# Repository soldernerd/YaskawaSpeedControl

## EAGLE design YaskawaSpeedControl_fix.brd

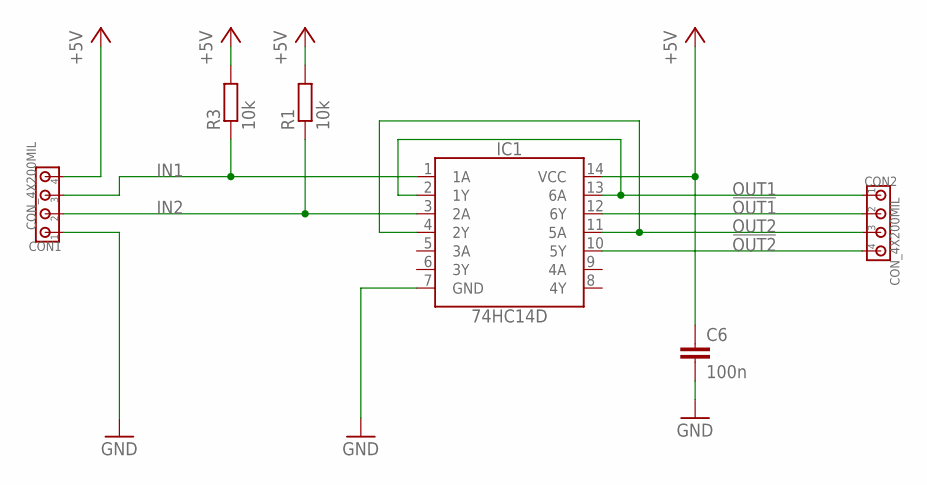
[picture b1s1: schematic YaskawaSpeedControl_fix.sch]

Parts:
C6: 100n; C0805
CON1, CON2: CON_4X200MIL; 200MIL_4X
IC1: 74HC14D; SO14
R1, R3: 10k; R0805

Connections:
!OUT1!: CON2.2, IC1.12 (6Y)
!OUT2!: CON2.4, IC1.10 (5Y)
+5V: C6.1, CON1.4, IC1.14 (VCC), R1.2, R3.2
GND: C6.2, CON1.1, IC1.7 (GND)
IN1: CON1.3, IC1.1 (1A), R3.1
IN2: CON1.2, IC1.3 (2A), R1.1
OUT1: CON2.1, IC1.2 (1Y), IC1.13 (6A)
OUT2: CON2.3, IC1.4 (2Y), IC1.11 (5A)

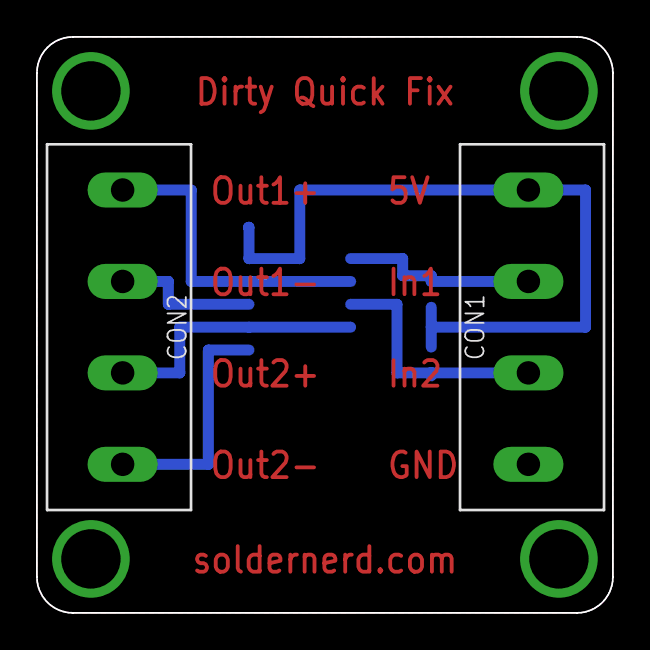
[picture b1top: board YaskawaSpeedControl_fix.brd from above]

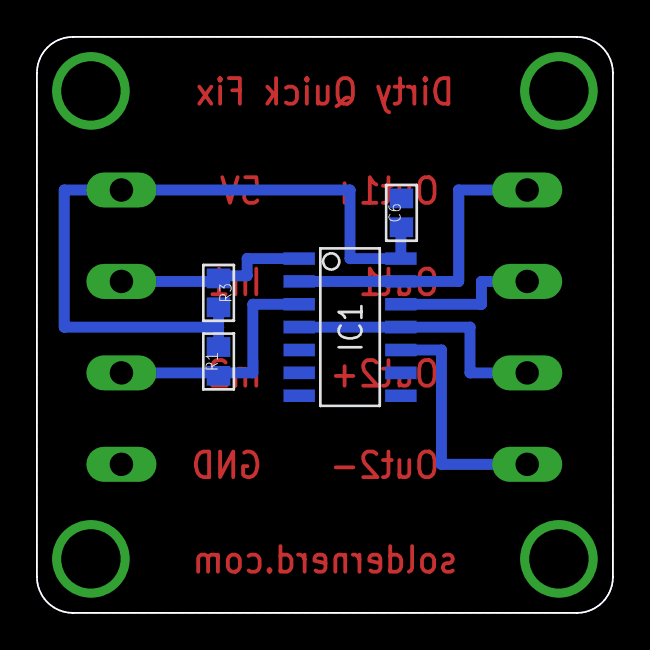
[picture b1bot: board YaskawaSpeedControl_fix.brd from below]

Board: 2 copper layers, 32.0 x 32.0 mm, 6 parts (4 on the bottom side), 8 nets.

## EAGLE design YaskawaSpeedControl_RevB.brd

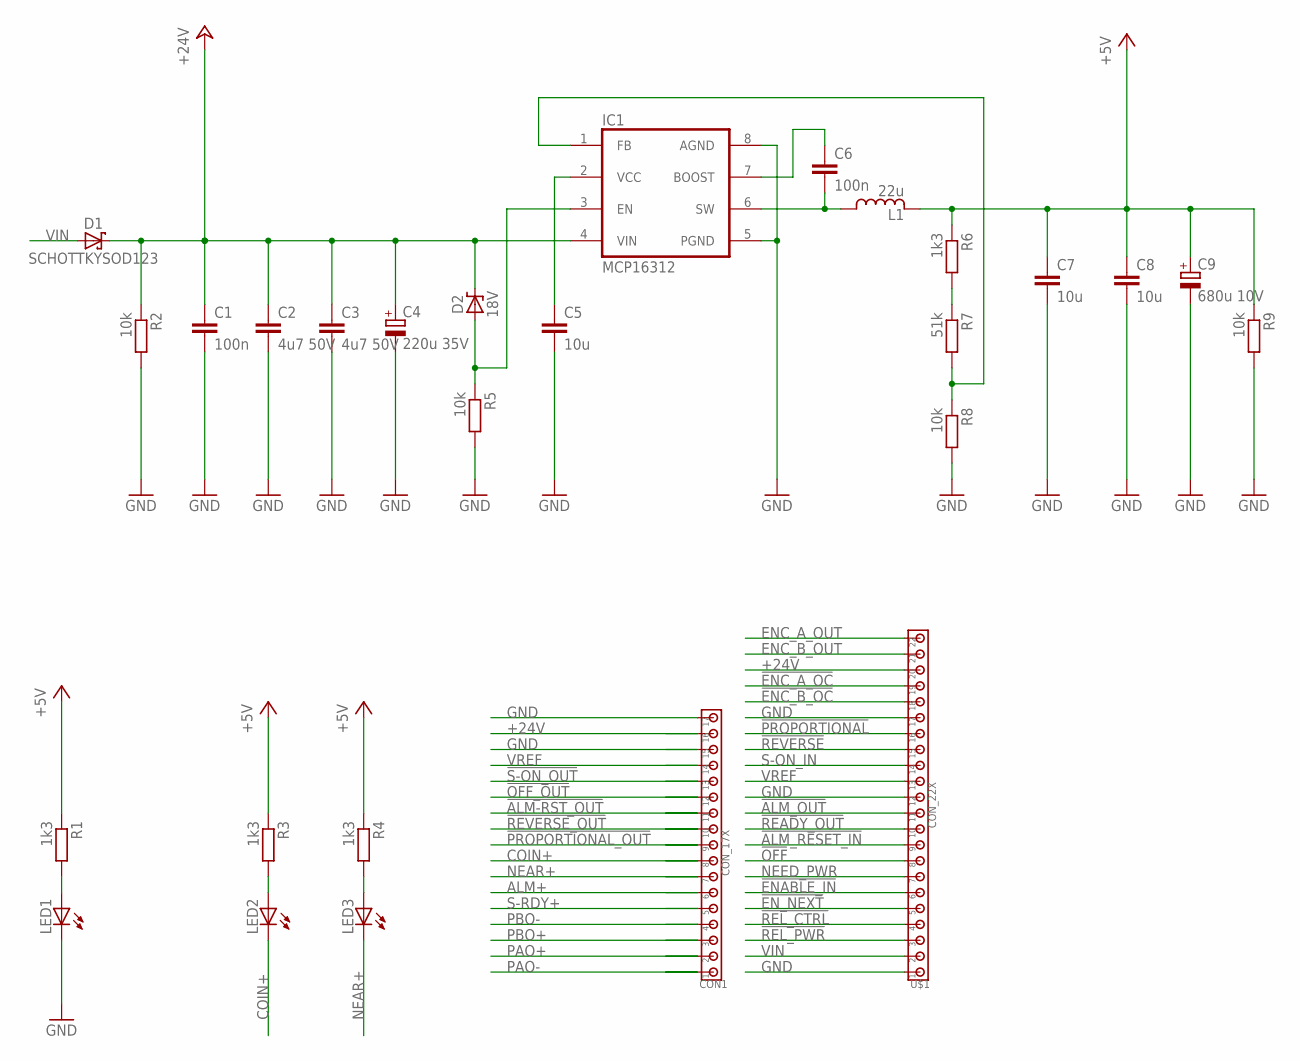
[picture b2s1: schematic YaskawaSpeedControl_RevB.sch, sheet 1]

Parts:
C1, C6: 100n; C0805
C2, C3: 4u7 50V; C1206
C4: 220u 35V; 8MM
C5, C7, C8: 10u; C0805
C9: 680u 10V; 8MM
CON1: CON_17X; 3.5MM_17X
D1: SCHOTTKYSOD123; SOD123
D2: 18V; SOD323
IC1: MCP16312; MSOP8
L1: 22u; LPS4018
LED1, LED2, LED3: LED0805_NB; LED0805_NOBOARDER
R1, R3, R4, R6: 1k3; R0805
R2, R5, R8, R9: 10k; R0805
R7: 51k; R0805
U$1: CON_22X; 3.5MM_22X

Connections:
!ALM-RST_OUT!: CON1.11; also elsewhere on the board
!ALM_OUT!: U$1.11; also elsewhere on the board
!ALM_RESET_IN!: U$1.9; also elsewhere on the board
!ENABLE_IN!: U$1.6; also elsewhere on the board
!ENC_A_OC!: U$1.19; also elsewhere on the board
!ENC_B_OC!: U$1.18; also elsewhere on the board
!EN_NEXT!: U$1.5; also elsewhere on the board
!OFF!: U$1.8; also elsewhere on the board
!OFF_OUT!: CON1.12; also elsewhere on the board
!PROPORTIONAL!: U$1.16; also elsewhere on the board
!PROPORTIONAL_OUT!: CON1.9; also elsewhere on the board
!READY_OUT!: U$1.10; also elsewhere on the board
!REL_CTRL!: U$1.4; also elsewhere on the board
!REL_PWR!: U$1.3; also elsewhere on the board
!REVERSE!: U$1.15; also elsewhere on the board
!REVERSE_OUT!: CON1.10; also elsewhere on the board
!S-ON_OUT!: CON1.13; also elsewhere on the board
+5V: C7.1, C8.1, C9.+, L1.2, R1.1, R3.1, R4.1, R6.1, R9.1; also elsewhere on the board
+24V: C1.1, C2.1, C3.1, C4.+, CON1.16, D1.C, D2.C, IC1.4 (VIN), R2.1, U$1.20; also elsewhere on the board
ALM+: CON1.6; also elsewhere on the board
BOOST: C6.1, IC1.7 (BOOST)
COIN+: CON1.8, LED2.C
ENC_A_OUT: U$1.22; also elsewhere on the board
ENC_B_OUT: U$1.21; also elsewhere on the board
GND: C1.2, C2.2, C3.2, C4.-, C5.2, C7.2, C8.2, C9.-, CON1.15, CON1.17, IC1.5 (PGND), IC1.8 (AGND), LED1.C, R2.2, R5.2, R8.2, R9.2, U$1.1, U$1.12, U$1.17; also elsewhere on the board
unnamed: IC1.1 (FB), R7.2, R8.1
unnamed: LED2.A, R3.2
unnamed: LED3.A, R4.2
unnamed: LED1.A, R1.2
unnamed: D2.A, IC1.3 (EN), R5.1
unnamed: R6.2, R7.1
unnamed: C5.1, IC1.2 (VCC)
NEAR+: CON1.7, LED3.C
NEED_PWR: U$1.7; also elsewhere on the board
PAO+: CON1.2; also elsewhere on the board
PAO-: CON1.1; also elsewhere on the board
PBO+: CON1.3; also elsewhere on the board
PBO-: CON1.4; also elsewhere on the board
S-ON_IN: U$1.14; also elsewhere on the board
S-RDY+: CON1.5; also elsewhere on the board
SWITCH: C6.2, IC1.6 (SW), L1.1
VIN: D1.A, U$1.2
VREF: CON1.14, U$1.13

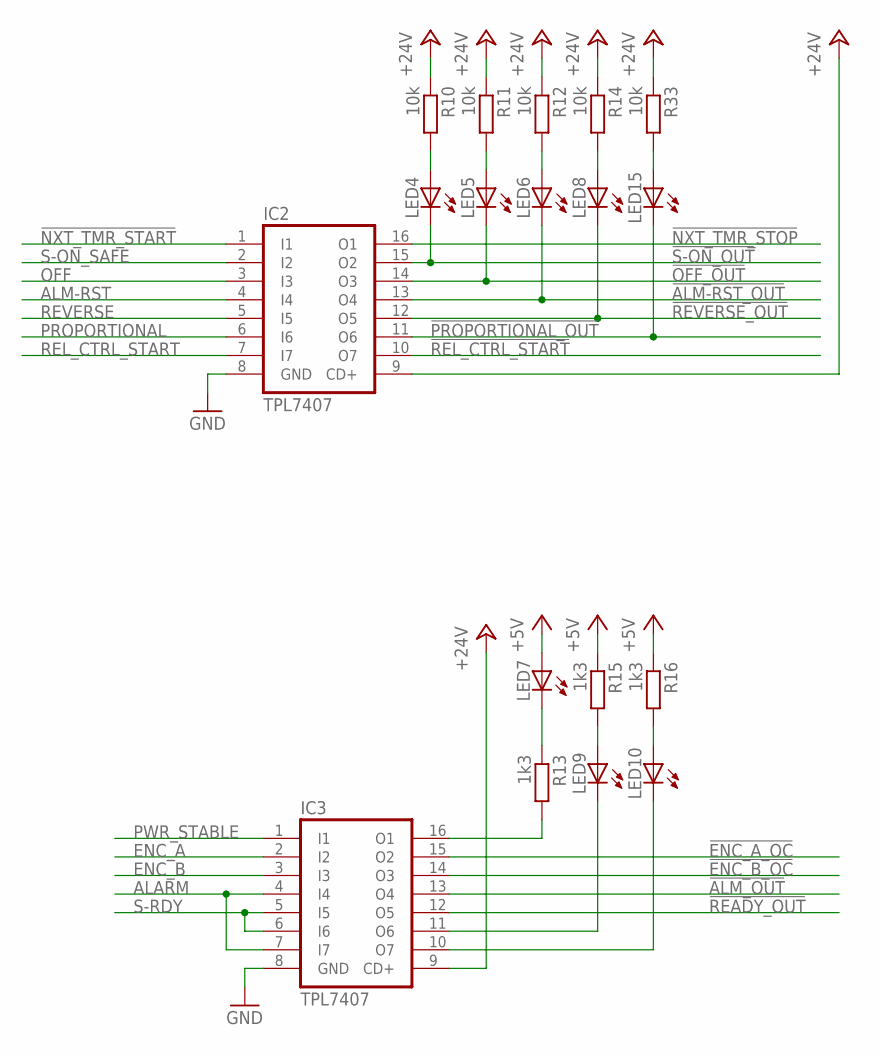
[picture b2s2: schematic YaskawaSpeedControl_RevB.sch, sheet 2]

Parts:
IC2, IC3: TPL7407; SO16
LED4, LED5, LED6, LED7, LED8, LED9, LED10, LED15: LED0805_NB; LED0805_NOBOARDER
R10, R11, R12, R14, R33: 10k; R0805
R13, R15, R16: 1k3; R0805

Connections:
!ALM-RST_OUT!: IC2.13 (O4), LED6.C; also elsewhere on the board
!ALM_OUT!: IC3.13 (O4); also elsewhere on the board
!ALM_OUT_LED!: IC3.10 (O7), LED10.C
!ENC_A_OC!: IC3.15 (O2); also elsewhere on the board
!ENC_B_OC!: IC3.14 (O3); also elsewhere on the board
!NXT_TMR_START!: IC2.1 (I1); also elsewhere on the board
!NXT_TMR_STOP!: IC2.16 (O1); also elsewhere on the board
!OFF_OUT!: IC2.14 (O3), LED5.C; also elsewhere on the board
!PROPORTIONAL_OUT!: IC2.11 (O6), LED15.C; also elsewhere on the board
!READY_OUT!: IC3.12 (O5); also elsewhere on the board
!READY_OUT_LED!: IC3.11 (O6), LED9.C
!REL_CTRL_START!: IC2.10 (O7); also elsewhere on the board
!REVERSE_OUT!: IC2.12 (O5), LED8.C; also elsewhere on the board
!S-ON_OUT!: IC2.15 (O2), LED4.C; also elsewhere on the board
+5V: LED7.A, R15.1, R16.1; also elsewhere on the board
+24V: IC2.9 (CD+), IC3.9 (CD+), R10.1, R11.1, R12.1, R14.1, R33.1; also elsewhere on the board
ALARM: IC3.4 (I4), IC3.7 (I7); also elsewhere on the board
ALM-RST: IC2.4 (I4); also elsewhere on the board
ENC_A: IC3.2 (I2); also elsewhere on the board
ENC_B: IC3.3 (I3); also elsewhere on the board
GND: IC2.8 (GND), IC3.8 (GND); also elsewhere on the board
unnamed: LED7.C, R13.1
unnamed: LED15.A, R33.2
unnamed: LED4.A, R10.2
unnamed: IC3.16 (O1), R13.2
unnamed: LED5.A, R11.2
unnamed: LED6.A, R12.2
unnamed: LED8.A, R14.2
unnamed: LED9.A, R15.2
unnamed: LED10.A, R16.2
OFF: IC2.3 (I3); also elsewhere on the board
PROPORTIONAL: IC2.6 (I6); also elsewhere on the board
PWR_STABLE: IC3.1 (I1); also elsewhere on the board
REL_CTRL_START: IC2.7 (I7); also elsewhere on the board
REVERSE: IC2.5 (I5); also elsewhere on the board
S-ON_SAFE: IC2.2 (I2); also elsewhere on the board
S-RDY: IC3.5 (I5), IC3.6 (I6); also elsewhere on the board

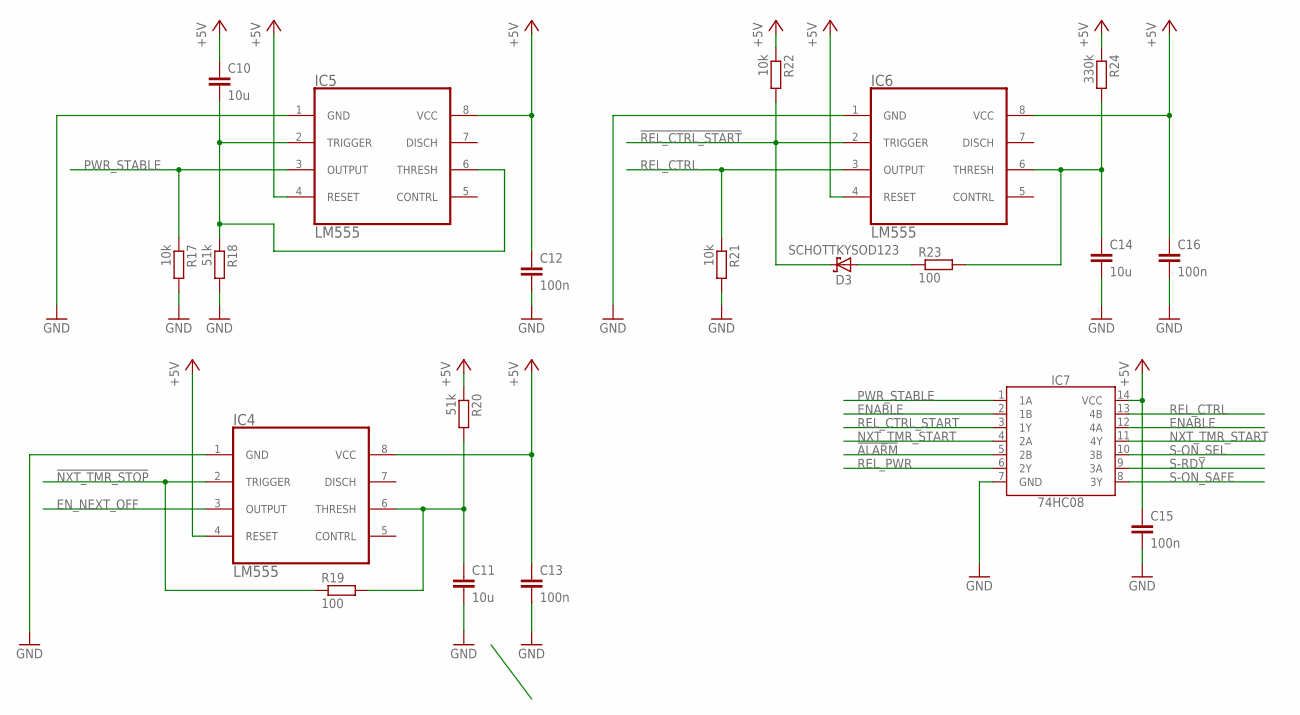
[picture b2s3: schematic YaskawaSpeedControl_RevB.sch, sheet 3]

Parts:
C10, C11, C14: 10u; C0805
C12, C13, C15, C16: 100n; C0805
D3: SCHOTTKYSOD123; SOD123
IC4, IC5, IC6: LM555; SOIC8
IC7: 74HC08; SO14
R17, R21, R22: 10k; R0805
R18, R20: 51k; R0805
R19, R23: 100; R0805
R24: 330k; R0805

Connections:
!ALARM!: IC7.5 (2B); also elsewhere on the board
!NXT_TMR_STOP!: IC4.2 (TRIGGER), R19.1; also elsewhere on the board
!REL_CTRL_START!: D3.C, IC6.2 (TRIGGER), R22.2; also elsewhere on the board
+5V: C10.1, C12.1, C13.1, C15.1, C16.1, IC4.4 (RESET), IC4.8 (VCC), IC5.4 (RESET), IC5.8 (VCC), IC6.4 (RESET), IC6.8 (VCC), IC7.14 (VCC), R20.1, R22.1, R24.1; also elsewhere on the board
ENABLE: IC7.2 (1B), IC7.12 (4A); also elsewhere on the board
EN_NEXT_OFF: IC4.3 (OUTPUT); also elsewhere on the board
GND: C11.2, C12.2, C13.2, C14.2, C15.2, C16.2, IC4.1 (GND), IC5.1 (GND), IC6.1 (GND), IC7.7 (GND), R17.2, R18.2, R21.2; also elsewhere on the board
unnamed: C10.2, IC5.2 (TRIGGER), IC5.6 (THRESH), R18.1
unnamed: C11.1, IC4.6 (THRESH), R19.2, R20.2
unnamed: C14.1, IC6.6 (THRESH), R23.2, R24.2
unnamed: D3.A, R23.1
NXT_TMR_START: IC7.4 (2A), IC7.11 (4Y); also elsewhere on the board
PWR_STABLE: IC5.3 (OUTPUT), IC7.1 (1A), R17.1; also elsewhere on the board
REL_CTRL: IC6.3 (OUTPUT), IC7.13 (4B), R21.1; also elsewhere on the board
REL_CTRL_START: IC7.3 (1Y); also elsewhere on the board
REL_PWR: IC7.6 (2Y); also elsewhere on the board
S-ON_SAFE: IC7.8 (3Y); also elsewhere on the board
S-ON_SEL: IC7.10 (3B); also elsewhere on the board
S-RDY: IC7.9 (3A); also elsewhere on the board

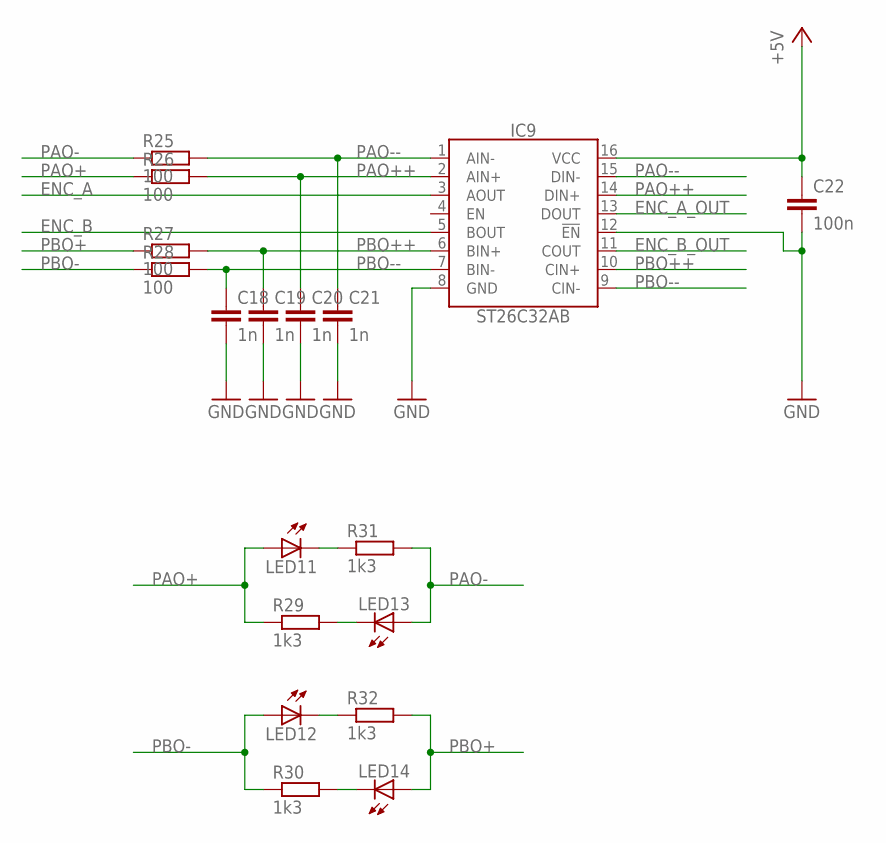
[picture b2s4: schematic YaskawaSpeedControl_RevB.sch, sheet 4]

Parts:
C18, C19, C20, C21: 1n; C0805
C22: 100n; C0805
IC9: ST26C32AB; SO16
LED11, LED12, LED13, LED14: LED0805_NB; LED0805_NOBOARDER
R25, R26, R27, R28: 100; R0805
R29, R30, R31, R32: 1k3; R0805

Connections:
+5V: C22.1, IC9.16 (VCC); also elsewhere on the board
ENC_A: IC9.3 (AOUT); also elsewhere on the board
ENC_A_OUT: IC9.13 (DOUT); also elsewhere on the board
ENC_B: IC9.5 (BOUT); also elsewhere on the board
ENC_B_OUT: IC9.11 (COUT); also elsewhere on the board
GND: C18.2, C19.2, C20.2, C21.2, C22.2, IC9.8 (GND), IC9.12 (!EN!); also elsewhere on the board
unnamed: LED11.C, R31.1
unnamed: LED12.C, R32.1
unnamed: LED13.C, R29.2
unnamed: LED14.C, R30.2
PAO+: LED11.A, R26.1, R29.1; also elsewhere on the board
PAO++: C20.1, IC9.2 (AIN+), IC9.14 (DIN+), R26.2
PAO-: LED13.A, R25.1, R31.2; also elsewhere on the board
PAO--: C21.1, IC9.1 (AIN-), IC9.15 (DIN-), R25.2
PBO+: LED14.A, R27.1, R32.2; also elsewhere on the board
PBO++: C19.1, IC9.6 (BIN+), IC9.10 (CIN+), R27.2
PBO-: LED12.A, R28.1, R30.1; also elsewhere on the board
PBO--: C18.1, IC9.7 (BIN-), IC9.9 (CIN-), R28.2

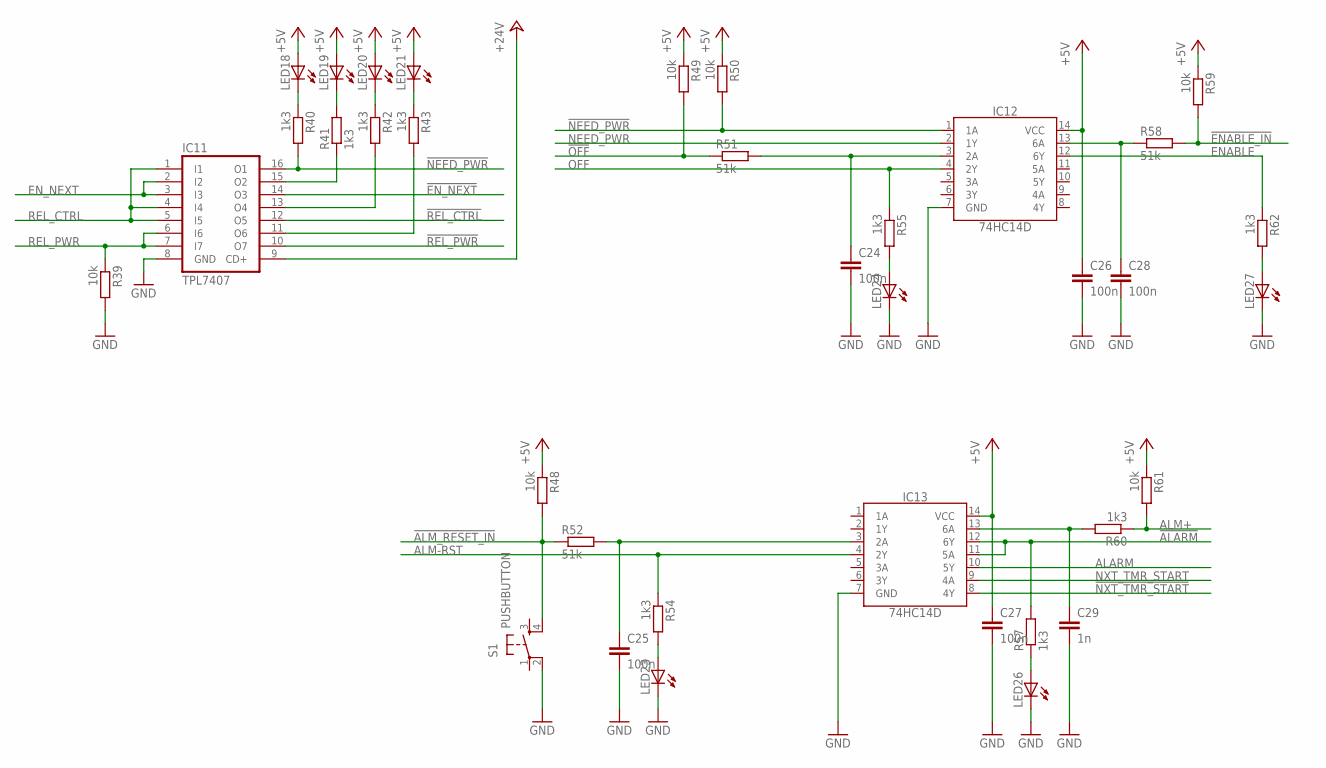
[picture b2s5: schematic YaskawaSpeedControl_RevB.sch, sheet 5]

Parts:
C24, C25, C26, C27, C28: 100n; C0805
C29: 1n; C0805
IC11: TPL7407; SO16
IC12, IC13: 74HC14D; SO14
LED18, LED19, LED20, LED21, LED23, LED24, LED26, LED27: LED0805_NB; LED0805_NOBOARDER
R39, R48, R49, R50, R59, R61: 10k; R0805
R40, R41, R42, R43, R54, R55, R57, R60, R62: 1k3; R0805
R51, R52, R58: 51k; R0805
S1: PUSHBUTTON; TE_FSMJSM

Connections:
!ALARM!: IC13.11 (5A), IC13.12 (6Y), R57.2; also elsewhere on the board
!ALM_RESET_IN!: R48.2, R52.1, S1.4 (S1); also elsewhere on the board
!ENABLE_IN!: R58.2, R59.2; also elsewhere on the board
!EN_NEXT!: IC11.14 (O3); also elsewhere on the board
!EN_NEXT_LED!: IC11.15 (O2), R41.1
!NEED_PWR!: IC11.16 (O1), IC12.1 (1A), R40.2, R50.2
!NXT_TMR_START!: IC13.8 (4Y); also elsewhere on the board
!OFF!: R49.2, R51.1; also elsewhere on the board
!REL_CTRL!: IC11.12 (O5); also elsewhere on the board
!REL_CTRL_LED!: IC11.13 (O4), R42.2
!REL_PWR!: IC11.10 (O7); also elsewhere on the board
!REL_PWR_LED!: IC11.11 (O6), R43.2
+5V: C26.1, C27.1, IC12.14 (VCC), IC13.14 (VCC), LED18.A, LED19.A, LED20.A, LED21.A, R48.1, R49.1, R50.1, R59.1, R61.1; also elsewhere on the board
+24V: IC11.9 (CD+); also elsewhere on the board
ALARM: IC13.10 (5Y); also elsewhere on the board
ALM+: R60.1, R61.2; also elsewhere on the board
ALM++: C29.1, IC13.13 (6A), R60.2
ALM-RST: IC13.4 (2Y), R54.1; also elsewhere on the board
ENABLE: IC12.12 (6Y), R62.1; also elsewhere on the board
EN_NEXT: IC11.2 (I2), IC11.3 (I3); also elsewhere on the board
GND: C24.2, C25.2, C26.2, C27.2, C28.2, C29.2, IC11.8 (GND), IC12.7 (GND), IC13.7 (GND), LED23.C, LED24.C, LED26.C, LED27.C, R39.2, S1.2 (P1); also elsewhere on the board
unnamed: C28.1, IC12.13 (6A), R58.1
unnamed: C25.1, IC13.3 (2A), R52.2
unnamed: C24.1, IC12.3 (2A), R51.2
unnamed: LED23.A, R54.2
unnamed: LED24.A, R55.2
unnamed: LED19.C, R41.2
unnamed: LED18.C, R40.1
unnamed: LED20.C, R42.1
unnamed: LED21.C, R43.1
unnamed: LED27.A, R62.2
unnamed: LED26.A, R57.1
NEED_PWR: IC12.2 (1Y); also elsewhere on the board
NXT_TMR_START: IC13.9 (4A); also elsewhere on the board
OFF: IC12.4 (2Y), R55.1; also elsewhere on the board
REL_CTRL: IC11.1 (I1), IC11.4 (I4), IC11.5 (I5); also elsewhere on the board
REL_PWR: IC11.6 (I6), IC11.7 (I7), R39.1; also elsewhere on the board

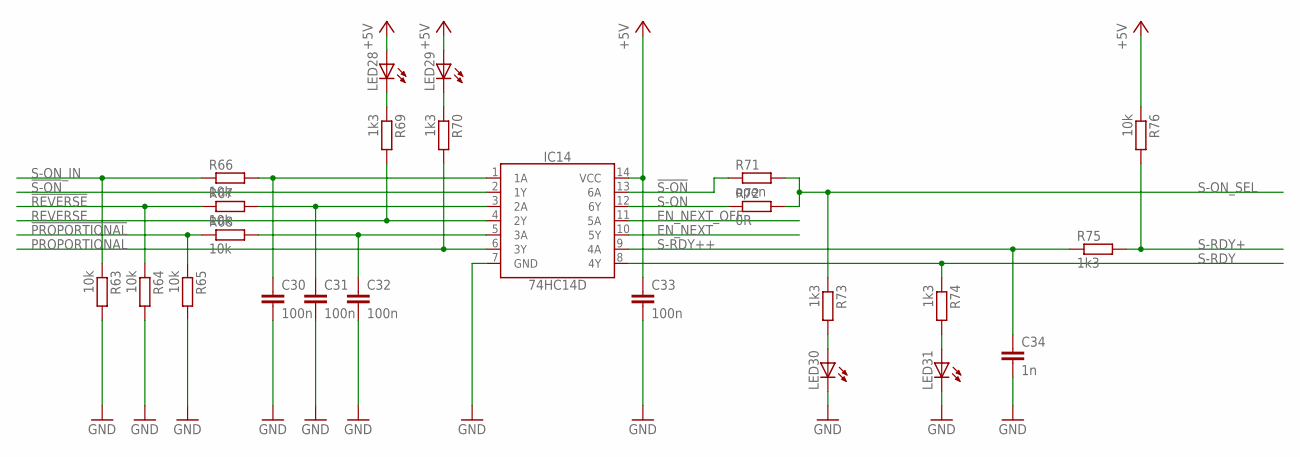
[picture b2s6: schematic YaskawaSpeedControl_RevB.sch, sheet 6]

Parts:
C30, C31, C32, C33: 100n; C0805
C34: 1n; C0805
IC14: 74HC14D; SO14
LED28, LED29, LED30, LED31: LED0805_NB; LED0805_NOBOARDER
R63, R64, R65, R66, R67, R68, R76: 10k; R0805
R69, R70, R73, R74, R75: 1k3; R0805
R71: open; R0805
R72: 0R; R0805

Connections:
!PROPORTIONAL!: R65.1, R68.1; also elsewhere on the board
!REVERSE!: R64.1, R67.1; also elsewhere on the board
!S-ON!: IC14.2 (1Y), IC14.13 (6A), R71.1
+5V: C33.1, IC14.14 (VCC), LED28.A, LED29.A, R76.1; also elsewhere on the board
EN_NEXT: IC14.10 (5Y); also elsewhere on the board
EN_NEXT_OFF: IC14.11 (5A); also elsewhere on the board
GND: C30.2, C31.2, C32.2, C33.2, C34.2, IC14.7 (GND), LED30.C, LED31.C, R63.2, R64.2, R65.2; also elsewhere on the board
unnamed: LED29.C, R70.1
unnamed: C30.1, IC14.1 (1A), R66.2
unnamed: C31.1, IC14.3 (2A), R67.2
unnamed: C32.1, IC14.5 (3A), R68.2
unnamed: LED28.C, R69.1
unnamed: LED30.A, R73.2
unnamed: LED31.A, R74.2
PROPORTIONAL: IC14.6 (3Y), R70.2; also elsewhere on the board
REVERSE: IC14.4 (2Y), R69.2; also elsewhere on the board
S-ON: IC14.12 (6Y), R72.1
S-ON_IN: R63.1, R66.1; also elsewhere on the board
S-ON_SEL: R71.2, R72.2, R73.1; also elsewhere on the board
S-RDY: IC14.8 (4Y), R74.1; also elsewhere on the board
S-RDY+: R75.2, R76.2; also elsewhere on the board
S-RDY++: C34.1, IC14.9 (4A), R75.1

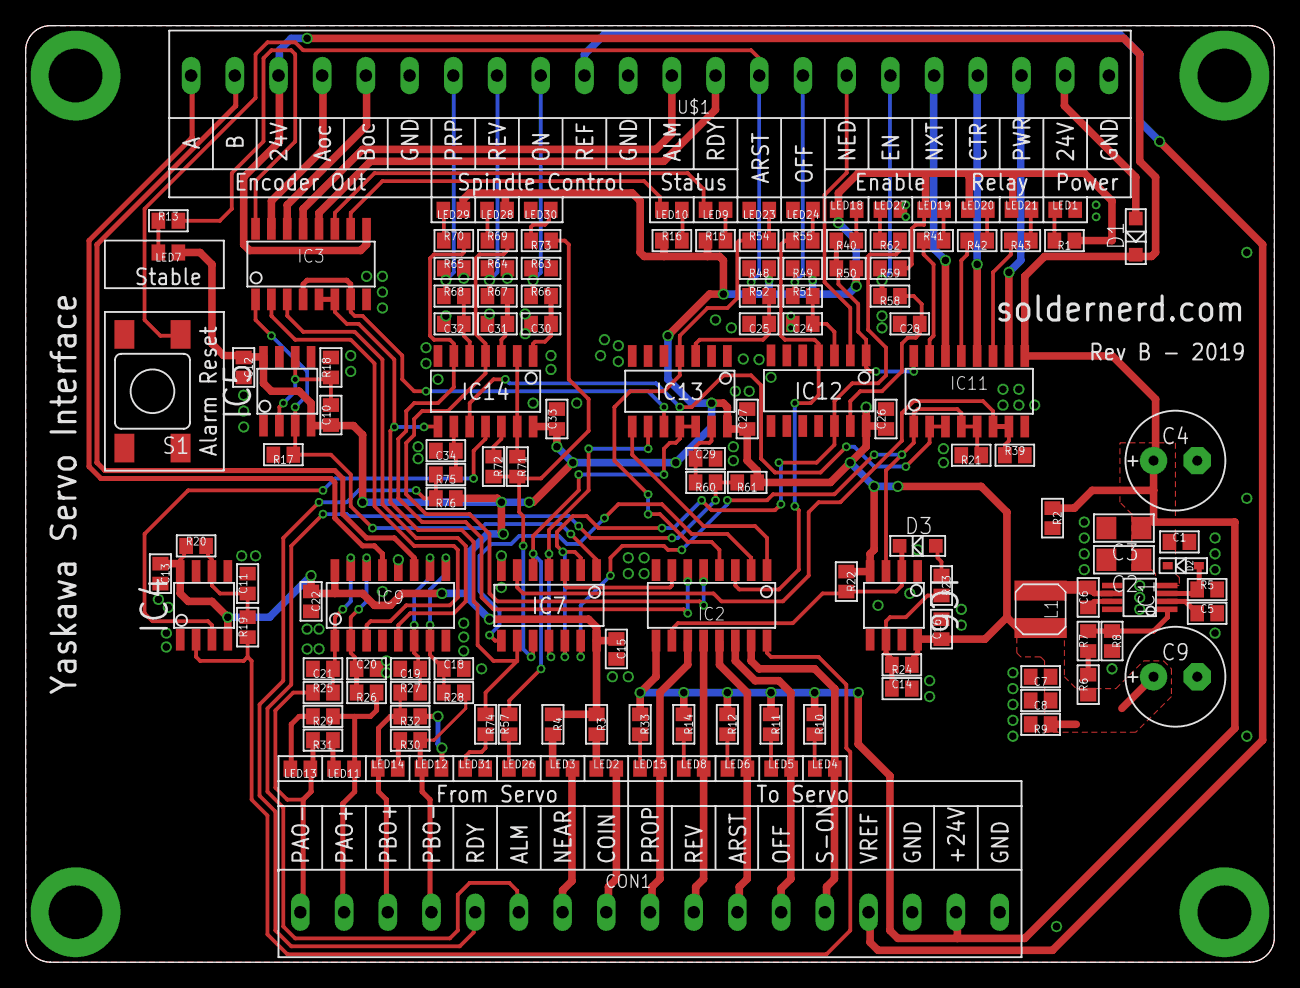
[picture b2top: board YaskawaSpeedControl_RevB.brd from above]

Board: 2 copper layers, 100.0 x 75.0 mm, 143 parts (0 on the bottom side), 114 nets.

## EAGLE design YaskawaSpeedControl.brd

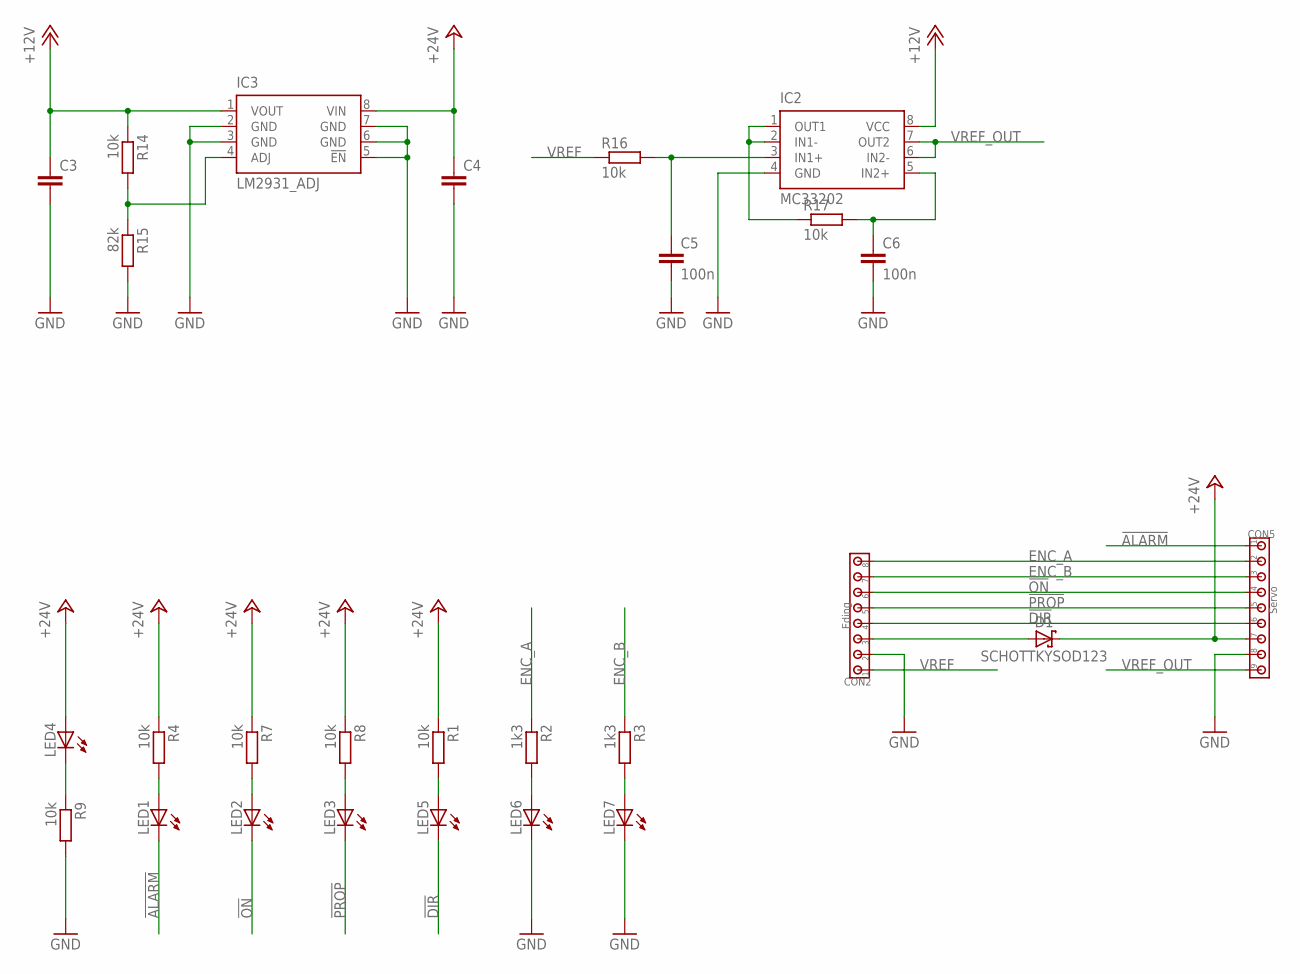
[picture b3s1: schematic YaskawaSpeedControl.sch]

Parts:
C3, C4: CC1206; C1206
C5, C6: 100n; C0805
CON2: Eding; 3.5MM_8X
CON5: Servo; 3.5MM_9X
D1: SCHOTTKYSOD123; SOD123
IC2: MC33202; SOIC8
IC3: LM2931_ADJ; SOIC8
LED1, LED2, LED3, LED4, LED5, LED6, LED7: LED0805
R1, R4, R7, R8, R9, R14, R16, R17: 10k; R0805
R2, R3: 1k3; R0805
R15: 82k; R0805

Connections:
!ALARM!: CON5.1, LED1.C
!DIR!: CON2.4, CON5.6, LED5.C
!ON!: CON2.6, CON5.4, LED2.C
!PROP!: CON2.5, CON5.5, LED3.C
+12V: C3.1, IC2.8 (VCC), IC3.1 (VOUT), R14.1
+24V: C4.1, CON5.7, D1.C, IC3.8 (VIN), LED4.A, R1.1, R4.1, R7.1, R8.1
ENC_A: CON2.8, CON5.2, R2.1
ENC_B: CON2.7, CON5.3, R3.1
GND: C3.2, C4.2, C5.2, C6.2, CON2.2, CON5.8, IC2.4 (GND), IC3.2 (GND), IC3.3 (GND), IC3.5 (!EN!), IC3.6 (GND), IC3.7 (GND), LED6.C, LED7.C, R9.2, R15.2
unnamed: LED5.A, R1.2
unnamed: LED1.A, R4.2
unnamed: LED2.A, R7.2
unnamed: LED3.A, R8.2
unnamed: LED4.C, R9.1
unnamed: LED6.A, R2.2
unnamed: LED7.A, R3.2
unnamed: IC3.4 (ADJ), R14.2, R15.1
unnamed: CON2.3, D1.A
unnamed: IC2.1 (OUT1), IC2.2 (IN1-), R17.1
unnamed: C5.1, IC2.3 (IN1+), R16.2
unnamed: C6.1, IC2.5 (IN2+), R17.2
VREF: CON2.1, R16.1
VREF_OUT: CON5.9, IC2.6 (IN2-), IC2.7 (OUT2)

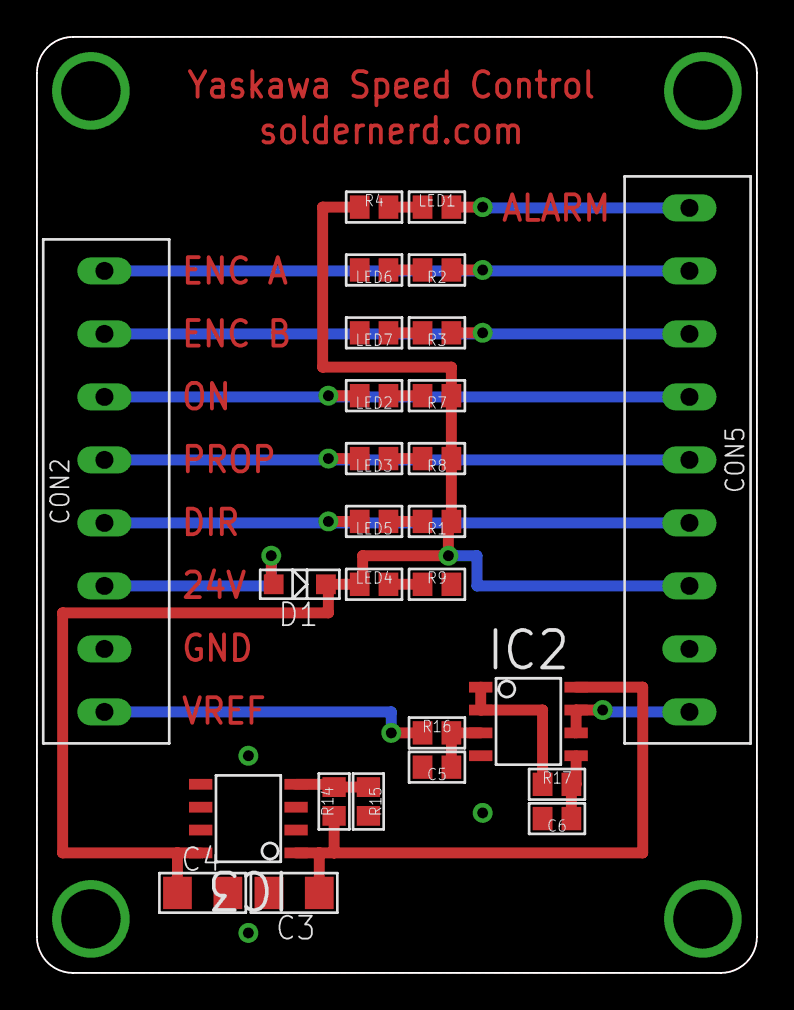
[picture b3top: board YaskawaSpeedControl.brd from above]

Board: 2 copper layers, 40.0 x 52.0 mm, 27 parts (0 on the bottom side), 23 nets.

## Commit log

2020-12-08 Initial commit. Mainly functional but might see another revision
